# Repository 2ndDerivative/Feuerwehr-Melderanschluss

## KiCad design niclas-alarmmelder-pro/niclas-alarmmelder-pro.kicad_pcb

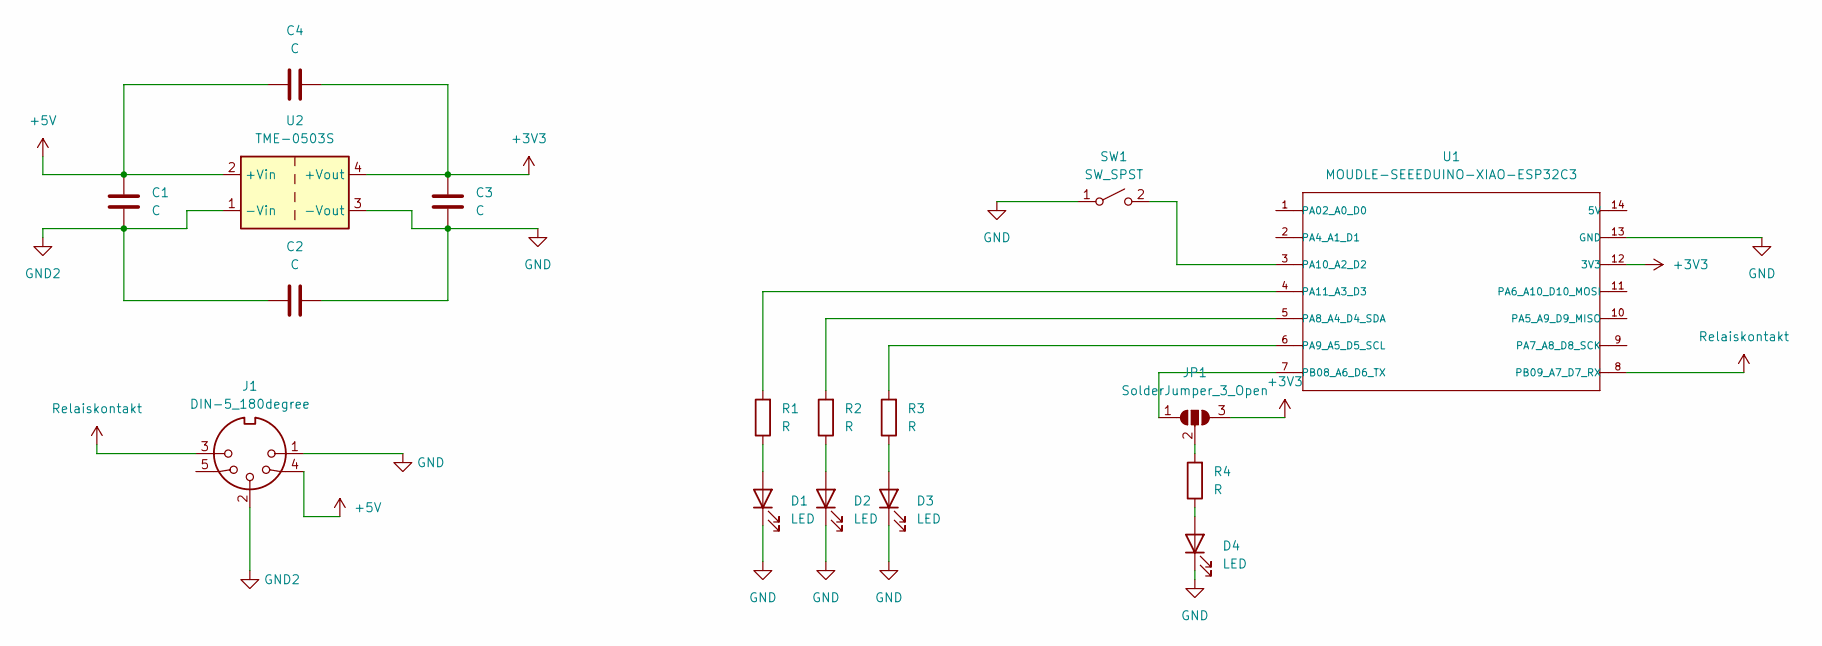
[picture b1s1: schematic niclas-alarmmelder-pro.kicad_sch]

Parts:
C1, C2, C3, C4: C; C_0603_1608Metric_Pad1.08x0.95mm_HandSolder
D1, D2, D3, D4: LED; LED_0805_2012Metric_Pad1.15x1.40mm_HandSolder
J1: DIN-5_180degree; 5pin din
JP1: SolderJumper_3_Open; SolderJumper-3_P2.0mm_Open_TrianglePad1.0x1.5mm_NumberLabels
R1, R2, R3, R4: R; R_0805_2012Metric_Pad1.20x1.40mm_HandSolder
SW1: SW_SPST; SW_DIP_SPSTx01_Slide_9.78x4.72mm_W7.62mm_P2.54mm
U1: MOUDLE-SEEEDUINO-XIAO-ESP32C3; MOUDLE14P-SMD-2.54-21X17.8MM
U2: TME-0503S; Converter_DCDC_TRACO_TME_03xxS_05xxS_12xxS_Single_THT

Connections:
+3V3: C3.2, C4.1, JP1.3 (B), U1.12 (3V3), U2.4 (+Vout)
+5V: C1.1, C4.2, J1.4, U2.2 (+Vin)
GND: C2.2, C3.1, D1.1 (K), D2.1 (K), D3.1 (K), D4.1 (K), J1.1, SW1.1 (A), U1.13 (GND), U2.3 (-Vout); also elsewhere on the board
GND2: C1.2, C2.1, J1.2, U2.1 (-Vin)
unnamed: D1.2 (A), R1.1
unnamed: D2.2 (A), R2.1
unnamed: D3.2 (A), R3.1
unnamed: D4.2 (A), R4.1
unnamed: JP1.1 (A), U1.7 (PB08_A6_D6_TX)
unnamed: JP1.2 (C), R4.2
unnamed: SW1.2 (B), U1.3 (PA10_A2_D2)
unnamed: R2.2, U1.5 (PA8_A4_D4_SDA)
unnamed: R3.2, U1.6 (PA9_A5_D5_SCL)
unnamed: R1.2, U1.4 (PA11_A3_D3)
Relaiskontakt: J1.3, U1.8 (PB09_A7_D7_RX)

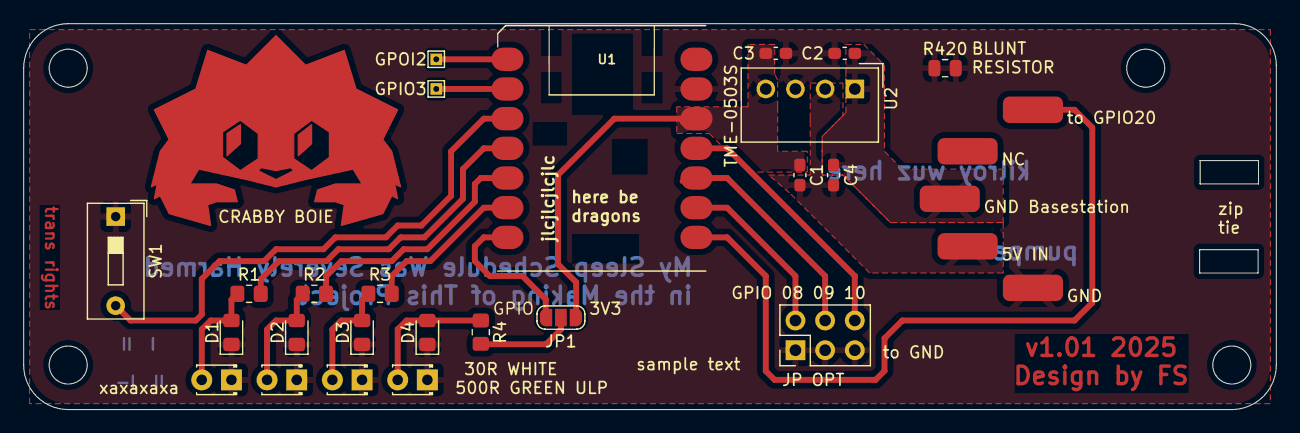
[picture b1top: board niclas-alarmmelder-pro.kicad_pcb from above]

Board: 2 copper layers, 107.2 x 33.0 mm, 22 parts (0 on the bottom side), 15 nets.

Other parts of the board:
CRABBY BOIE: Ferris
GPIO3: TestPoint_THTPad_1.0x1.0mm_Drill0.5mm
GPOI2: TestPoint_THTPad_1.0x1.0mm_Drill0.5mm
JP OPT: PinHeader_2x03_P2.54mm_Vertical
R420: R_0805_2012Metric

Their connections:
GND: JP OPT.1, JP OPT.3, JP OPT.5, R420.1, R420.2; also elsewhere on the board

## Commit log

2025-08-10 Initial
2025-08-10 metadata
2025-08-10 don't panic, just don't reenter hook when someone grabs the IO origin
2025-08-10 add loicense
2025-08-10 fix license file manifest key
2025-08-10 remove redundant license
2025-08-10 move to default main.rs setup
2025-08-10 remove cargo.toml comments
2025-08-10 put manual link into docs
2025-08-10 allow flexible toolchain build
2025-08-11 Add files via upload
    KiCad PCB Project added
2025-08-11 Create README.md
    ligma
2025-08-11 remove other redundant files and gitignore them
2025-08-11 release ready
    Sollte so funktionieren, eine Schraube mag oder mag nicht accessible sein je nach Schalter aber idc worst case reichen auch 2
2025-08-12 remove zip filse
2025-08-12 v1.1
    small fixes nothing to worry about :)
2025-08-12 reformat gitignore
